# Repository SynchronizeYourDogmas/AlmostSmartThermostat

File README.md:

# AlmostSmartThermostat

A home thermostat project based on the Particle Photon (https://www.particle.io/).

Notice: this thermostat simply switches the heating on/off and does not use OpenTherm to communicate with the heating/cooling appliance.
If you wan to go the Opentherm route, http://ihormelnyk.com/page/arduino_opentherm_controller and https://github.com/sulicz/Arduino-OpenTherm are good places to start

The sensor is a Bosch BME680 from Pimoroni (https://shop.pimoroni.com/products/bme680), communicating via the I2C-interface of the Photon.

Sensor data available via the Particle cloud:
  - Temperature (°C)
  - Relative humidity
  - Air Pressure (hPa)
  - Air Quality (gas resistance expressed in kOhm, lower is worse)
  - Altitude

A small 128x64 Oled display (SSD1306) is connect via software SPI and shows
  - Temperature (°C), Air Pressure (hPa), Air Quality alternating every 15s
  - Local time
  - Indicators for heating and desired temperature

All credits to Adafruit (https://www.adafruit.com/) for the work on the drivers and the Particle community for porting them :)

A default temperature table is stored in the simulated EEPROM of the Particle, this allows basic functionality without internet connection.
The table design:
  - 7 days times 24 hours divided in periods of 15 minutes
  - for each period there are 4 options represented by bit values
    '00' undefined
    '01' night temperature
    '10' economy temperature
    '11' sunny temperature
    for a total of 168 bytes (small enough to fit 1 cloud variable)

It is the intention to create a management webinterface in the near future.
At this moment there is only a temperature override function in the Particle console.

The logic sends signals to a L293DNE half-H driver, controlling a simple 3v/220v latching relay which switches the central heating on/off.
Adapt this for your personal situation.

An Eagle CAD schematic (and a Fritzing breadboard example) are available /doc 

Future work
- calibration
- design PCB to evolve from the breadboard design
- web interface
- making the air quality 'human readable'
- make a nice box to put everything in

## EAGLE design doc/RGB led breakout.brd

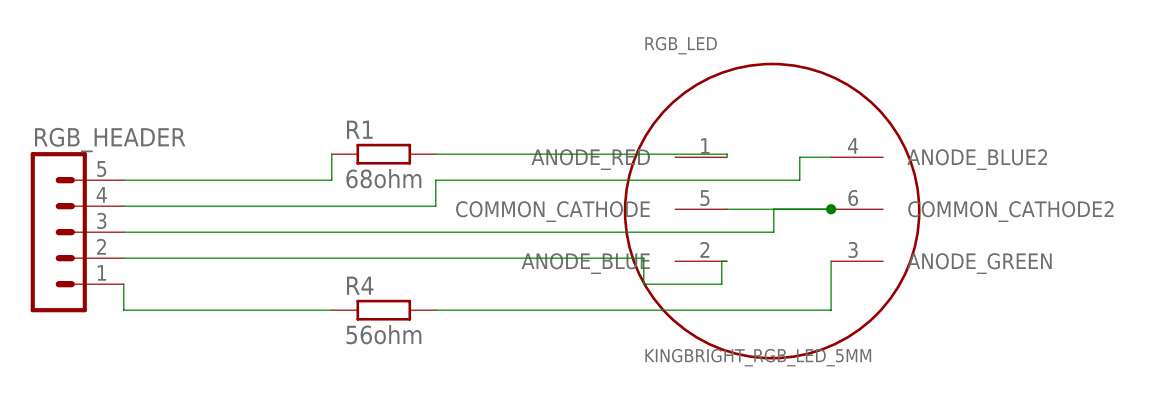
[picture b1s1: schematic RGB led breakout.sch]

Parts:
R1: 68ohm; 0207/7
R4: 56ohm; 0207/7
RGB_HEADER: MA05-1
RGB_LED: KINGBRIGHT_RGB_LED_5MM; LF5WAEMBGMBW

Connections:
CATHODE: RGB_HEADER.3, RGB_LED.5 (COMMON_CATHODE), RGB_LED.6 (COMMON_CATHODE2)
unnamed: R1.2, RGB_LED.1 (ANODE_RED)
unnamed: R4.2, RGB_LED.3 (ANODE_GREEN)
unnamed: R1.1, RGB_HEADER.5
unnamed: RGB_HEADER.4, RGB_LED.4 (ANODE_BLUE2)
unnamed: RGB_HEADER.2, RGB_LED.2 (ANODE_BLUE)
unnamed: R4.1, RGB_HEADER.1

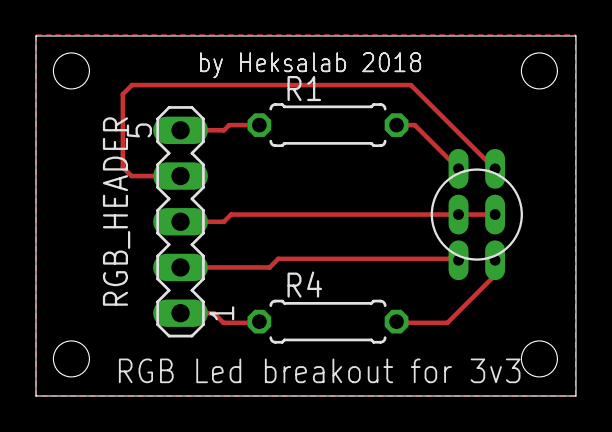
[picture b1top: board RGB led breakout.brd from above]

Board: 2 copper layers, 30.0 x 20.0 mm, 4 parts (0 on the bottom side), 7 nets.

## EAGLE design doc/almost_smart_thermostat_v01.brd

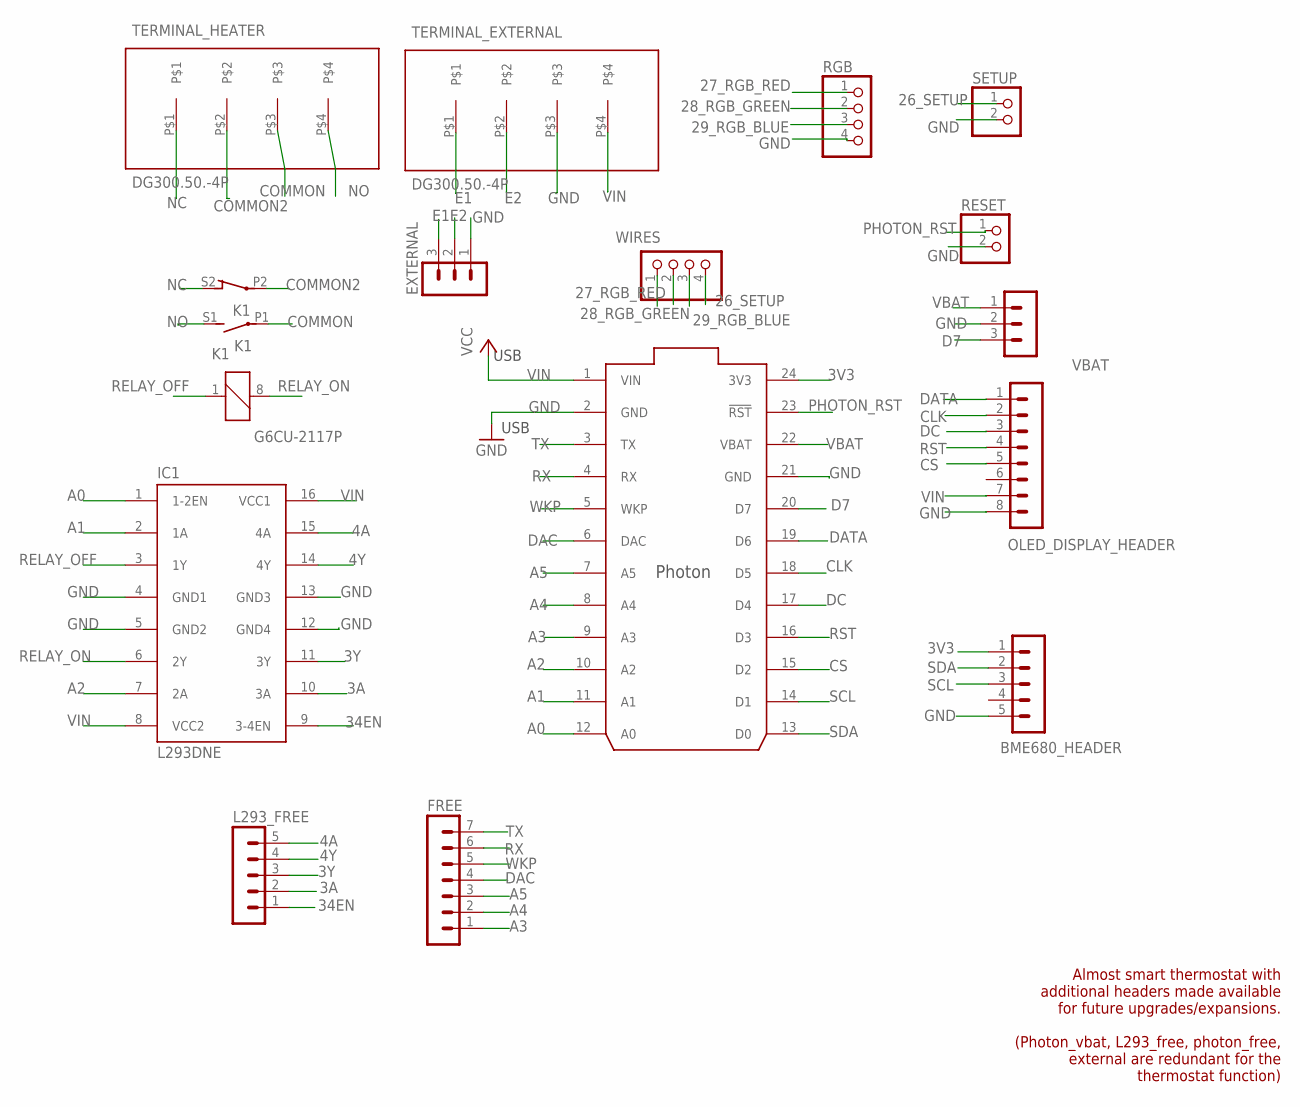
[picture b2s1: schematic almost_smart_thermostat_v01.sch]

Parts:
BME680_HEADER: MA05-1
EXTERNAL: MA03-1
FREE: MA07-1
IC1: L293DNE; DIL16
K1: G6CU-2117P; G6C-2117P
L293_FREE: MA05-1
OLED_DISPLAY_HEADER: MA08-1
RESET: PINHD-1X2; 1X02
RGB: PINHD-1X4; 1X04
SETUP: PINHD-1X2; 1X02
TERMINAL_EXTERNAL: DG300.50.-4P; DG300-5.0-4P
TERMINAL_HEATER: DG300.50.-4P; DG300-5.0-4P
U$1: PHOTON_WITH_HEADERS; PHOTON
VBAT: MA03-1
WIRES: PINHD-1X4; 1X04

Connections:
3A: IC1.10 (3A), L293_FREE.2
3V3: BME680_HEADER.1, U$1.24 (3V3)
3Y: IC1.11 (3Y), L293_FREE.3
4A: IC1.15 (4A), L293_FREE.5
4Y: IC1.14 (4Y), L293_FREE.4
26_SETUP: SETUP.1, WIRES.4
27_RGB_RED: RGB.1, WIRES.1
28_RGB_GREEN: RGB.2, WIRES.2
29_RGB_BLUE: RGB.3, WIRES.3
34EN: IC1.9 (3-4EN), L293_FREE.1
A0: IC1.1 (1-2EN), U$1.12 (A0)
A1: IC1.2 (1A), U$1.11 (A1)
A2: IC1.7 (2A), U$1.10 (A2)
A3: FREE.1, U$1.9 (A3)
A4: FREE.2, U$1.8 (A4)
A5: FREE.3, U$1.7 (A5)
CLK: OLED_DISPLAY_HEADER.2, U$1.18 (D5)
COMMON: K1.P1, TERMINAL_HEATER.P$3
COMMON2: K1.P2, TERMINAL_HEATER.P$2
CS: OLED_DISPLAY_HEADER.5, U$1.15 (D2)
D7: U$1.20 (D7), VBAT.3
DAC: FREE.4, U$1.6 (DAC)
DATA: OLED_DISPLAY_HEADER.1, U$1.19 (D6)
DC: OLED_DISPLAY_HEADER.3, U$1.17 (D4)
E1: EXTERNAL.3, TERMINAL_EXTERNAL.P$1
E2: EXTERNAL.2, TERMINAL_EXTERNAL.P$2
GND: BME680_HEADER.5, EXTERNAL.1, IC1.4 (GND1), IC1.5 (GND2), IC1.12 (GND4), IC1.13 (GND3), OLED_DISPLAY_HEADER.8, RESET.2, RGB.4, SETUP.2, TERMINAL_EXTERNAL.P$3, U$1.2 (GND), U$1.21 (GND), VBAT.2
NC: K1.S2 (O), TERMINAL_HEATER.P$1
NO: K1.S1 (S), TERMINAL_HEATER.P$4
PHOTON_RST: RESET.1, U$1.23 (!RST)
RELAY_OFF: IC1.3 (1Y), K1.1
RELAY_ON: IC1.6 (2Y), K1.8 (2)
RST: OLED_DISPLAY_HEADER.4, U$1.16 (D3)
RX: FREE.6, U$1.4 (RX)
SCL: BME680_HEADER.3, U$1.14 (D1)
SDA: BME680_HEADER.2, U$1.13 (D0)
TX: FREE.7, U$1.3 (TX)
VBAT: U$1.22 (VBAT), VBAT.1
VIN: IC1.8 (VCC2), IC1.16 (VCC1), OLED_DISPLAY_HEADER.7, TERMINAL_EXTERNAL.P$4, U$1.1 (VIN)
WKP: FREE.5, U$1.5 (WKP)

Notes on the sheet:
USB
Almost smart thermostat with additional headers made available for future upgrades/expansions. (Photon_vbat, L293_free, photon_free, external are redundant for the thermostat function)

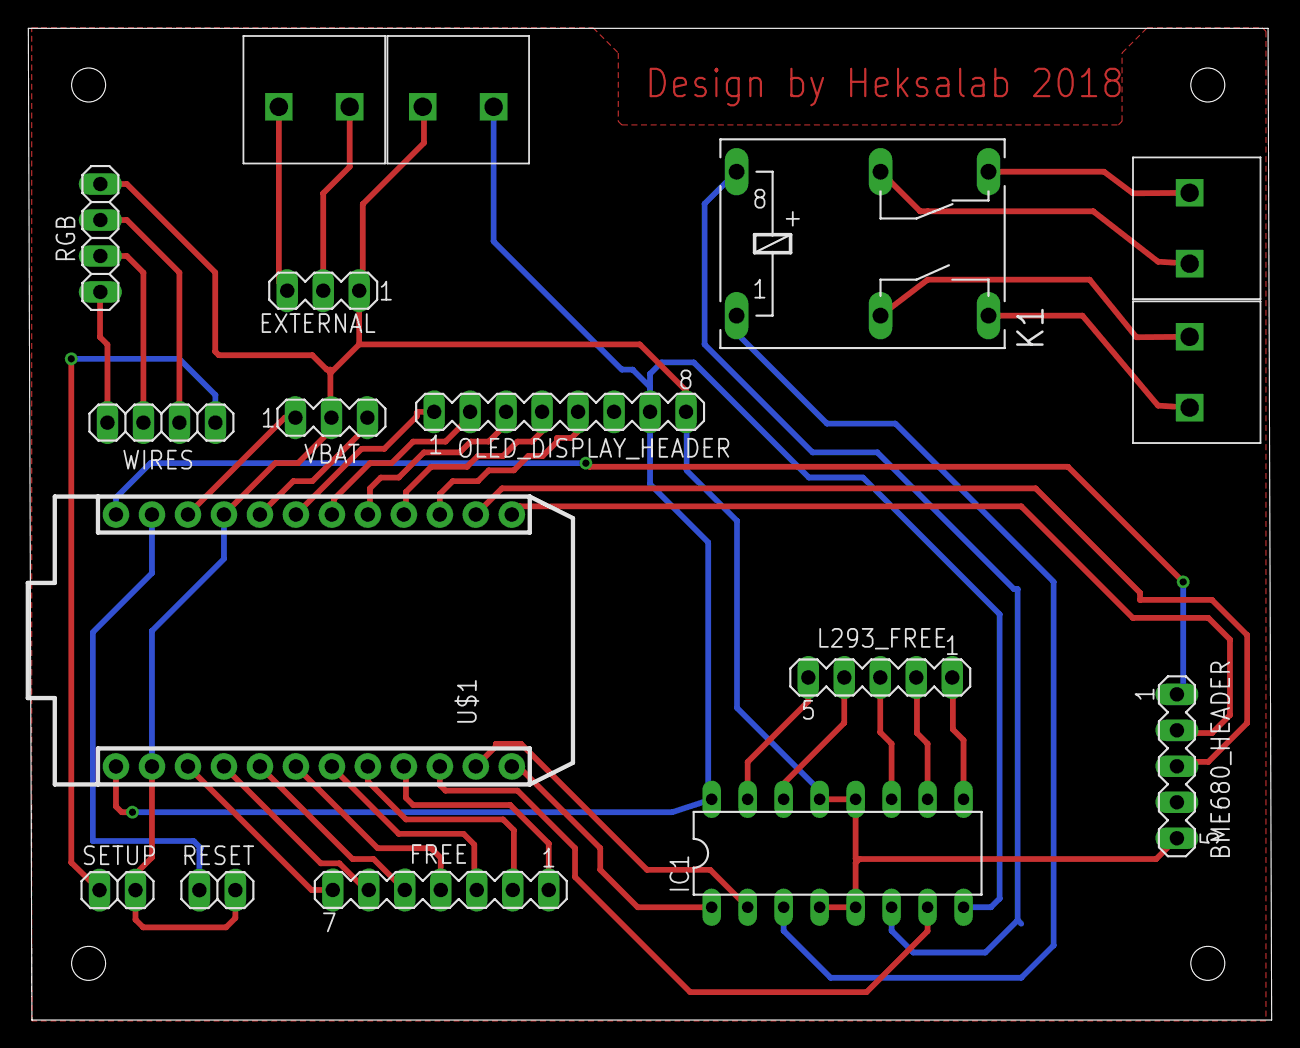
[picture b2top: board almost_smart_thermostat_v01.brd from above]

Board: 2 copper layers, 87.8 x 70.0 mm, 15 parts (0 on the bottom side), 40 nets.

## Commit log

2018-02-16 My IoT Home Thermostat project, based on particle photon Very much a work in progress :)
2018-02-19 Added EEPROM storage functionality
    EEPROM storage functionality for storing a timetable with different
    temperatures (night, eco, sunny) as defaults. In the future this table
    user manageable - nut not yet ;)
2018-02-19 Add heating indication cloud variable
    Added heating indication cloud variable and some polish
2018-02-21 Added Oled display and BME680 sensor
2018-02-21 DIsplaying air pressure on Oled screen
2018-02-21 Renamed files to match project name
2018-02-21 added credits in readme :)
2018-02-21 added frizting schematic
2018-02-28 Added Eagle schematic
    Added Eagle schematic and added notice about Opentherm communciation
2018-02-28 FIxed typo
2018-03-11 Updated Eagle schematics and pcb design
